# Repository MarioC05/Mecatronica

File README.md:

# Robot Sube-Escaleras

Proyecto de la asignatura **Mecatrónica** del **Grado en Ingeniería de Robótica Software** de la **Universidad Rey Juan Carlos (URJC)**.

## Componentes del grupo:

- Adrián Manzanares Romera: [Amanza17](https://github.com/Amanza17)
- Claudia Élez Mencía: [celezm](https://github.com/celezm)
- Mario Casero Sández: [MarioC05](https://github.com/MarioC05)
- Rebeca Castilla Puerta [rumbahuh](https://github.com/rumbahuh)

## Objetivo

Diseñar, fabricar y programar un robot terrestre capaz de **subir al menos un peldaño** de las escaleras del laboratorio III de la URJC, manteniendo la estabilidad y evitando obstáculos durante la aproximación.

### Requisitos principales

- Subir al menos un peldaño en **menos de 1 minuto**.
- Detectar y evitar obstáculos durante la aproximación, partiendo de **20 cm de la contrahuella**, dentro del tiempo establecido.
- No superar **25 × 25 × 25 cm** para el robot completo.
- Utilizar **baterías recargables**, sin alimentación por cable durante las pruebas.
- Diseñar y fabricar una **estructura propia**.
- Incorporar una interfaz para **iniciar y detener** el funcionamiento.
- Respetar la restricción de **locomoción sin ruedas** establecida en el enunciado.

## Diseño seleccionado

Durante la fase de diseño conceptual se estudiaron cuatro alternativas:

1. Robot cuadrúpedo tipo perro.
2. Robot bípedo con cuerpo horizontal y rueda loca delantera retráctil.
3. Robot serpiente modular.
4. Robot lineal tipo impresora 3D, con pie fijo y pie móvil.

La propuesta elegida para continuar el desarrollo es el **bípedo**. Consta de dos patas articuladas y un apoyo delantero mediante rueda loca que puede replegarse hacia atrás.

## Estructura del repositorio

```text
Mecatronica/
├── README.md
├── planificacion/
│   ├── diagrama_gantt
│   └── diagrama_pert
│   └── planificacion_nov
├── diseno_conceptual/
│   │   ├── matriz_calidad
│   │   └── matriz_seleccion
│   │   └── diseño_conceptual
├── diseno_detallado
│   ├── Eltronico.FCStd
│   ├── motores.pdf
│   └── piezas
│       ├── designed
│       │   ├── battery.FCStd
│       │   ├── ...
│       └── internet
│           ├── adafruit.FCStd
│           ├── ...
└── simulacion
    └── pybullet
        ├── eltronico.urdf
        ├── pybullet_meshes
        │   ├── Adafruit.stl
        │   ├── ...
        └── simulacion_estatica_escalon.py
└── eltronico_ws
    └── src  
        ├── eltronico
        ├── ir
        └── tui     
```

## Estado del proyecto

Actualmente, se está finalizando el montaje definitivo de las piezas del robot. El montaje de la electrónica está prácticamente finalizado, a expensas de la llegada de una PCB que integra los 2 reguladores de voltaje y algunas resistencias y la integración de un sensor infrarrojo para comandar al robot con un mando ir.

Respecto a la programación, se sigue trabajando en el controlador para la subida del escalón y en la migración e integración del código de MQTT y scripts de python a ROS2.

*Este es el robot a día 19 de noviembre*

En la carpeta [media](./media) se pueden encontrar distintas fotos y videos del montaje del robot y de pruebas de los motores.

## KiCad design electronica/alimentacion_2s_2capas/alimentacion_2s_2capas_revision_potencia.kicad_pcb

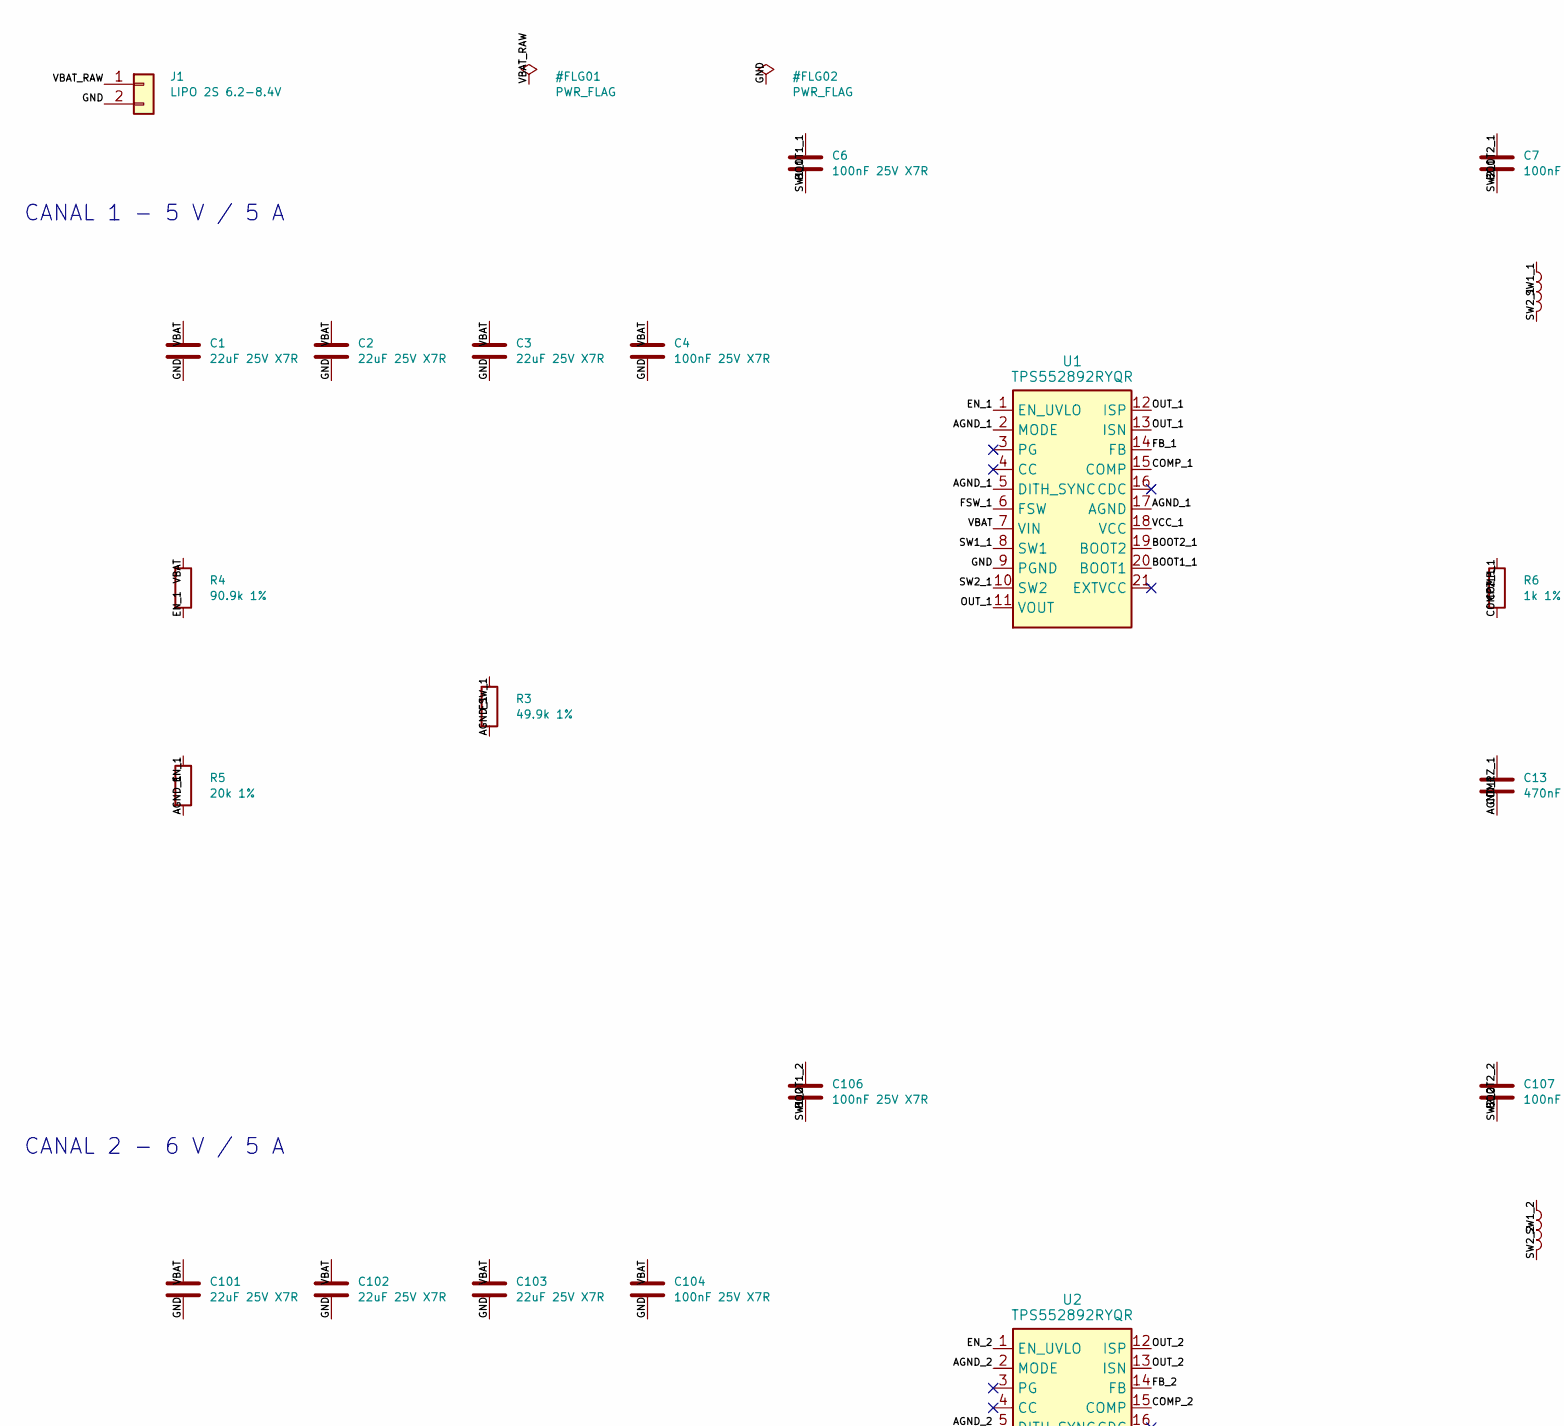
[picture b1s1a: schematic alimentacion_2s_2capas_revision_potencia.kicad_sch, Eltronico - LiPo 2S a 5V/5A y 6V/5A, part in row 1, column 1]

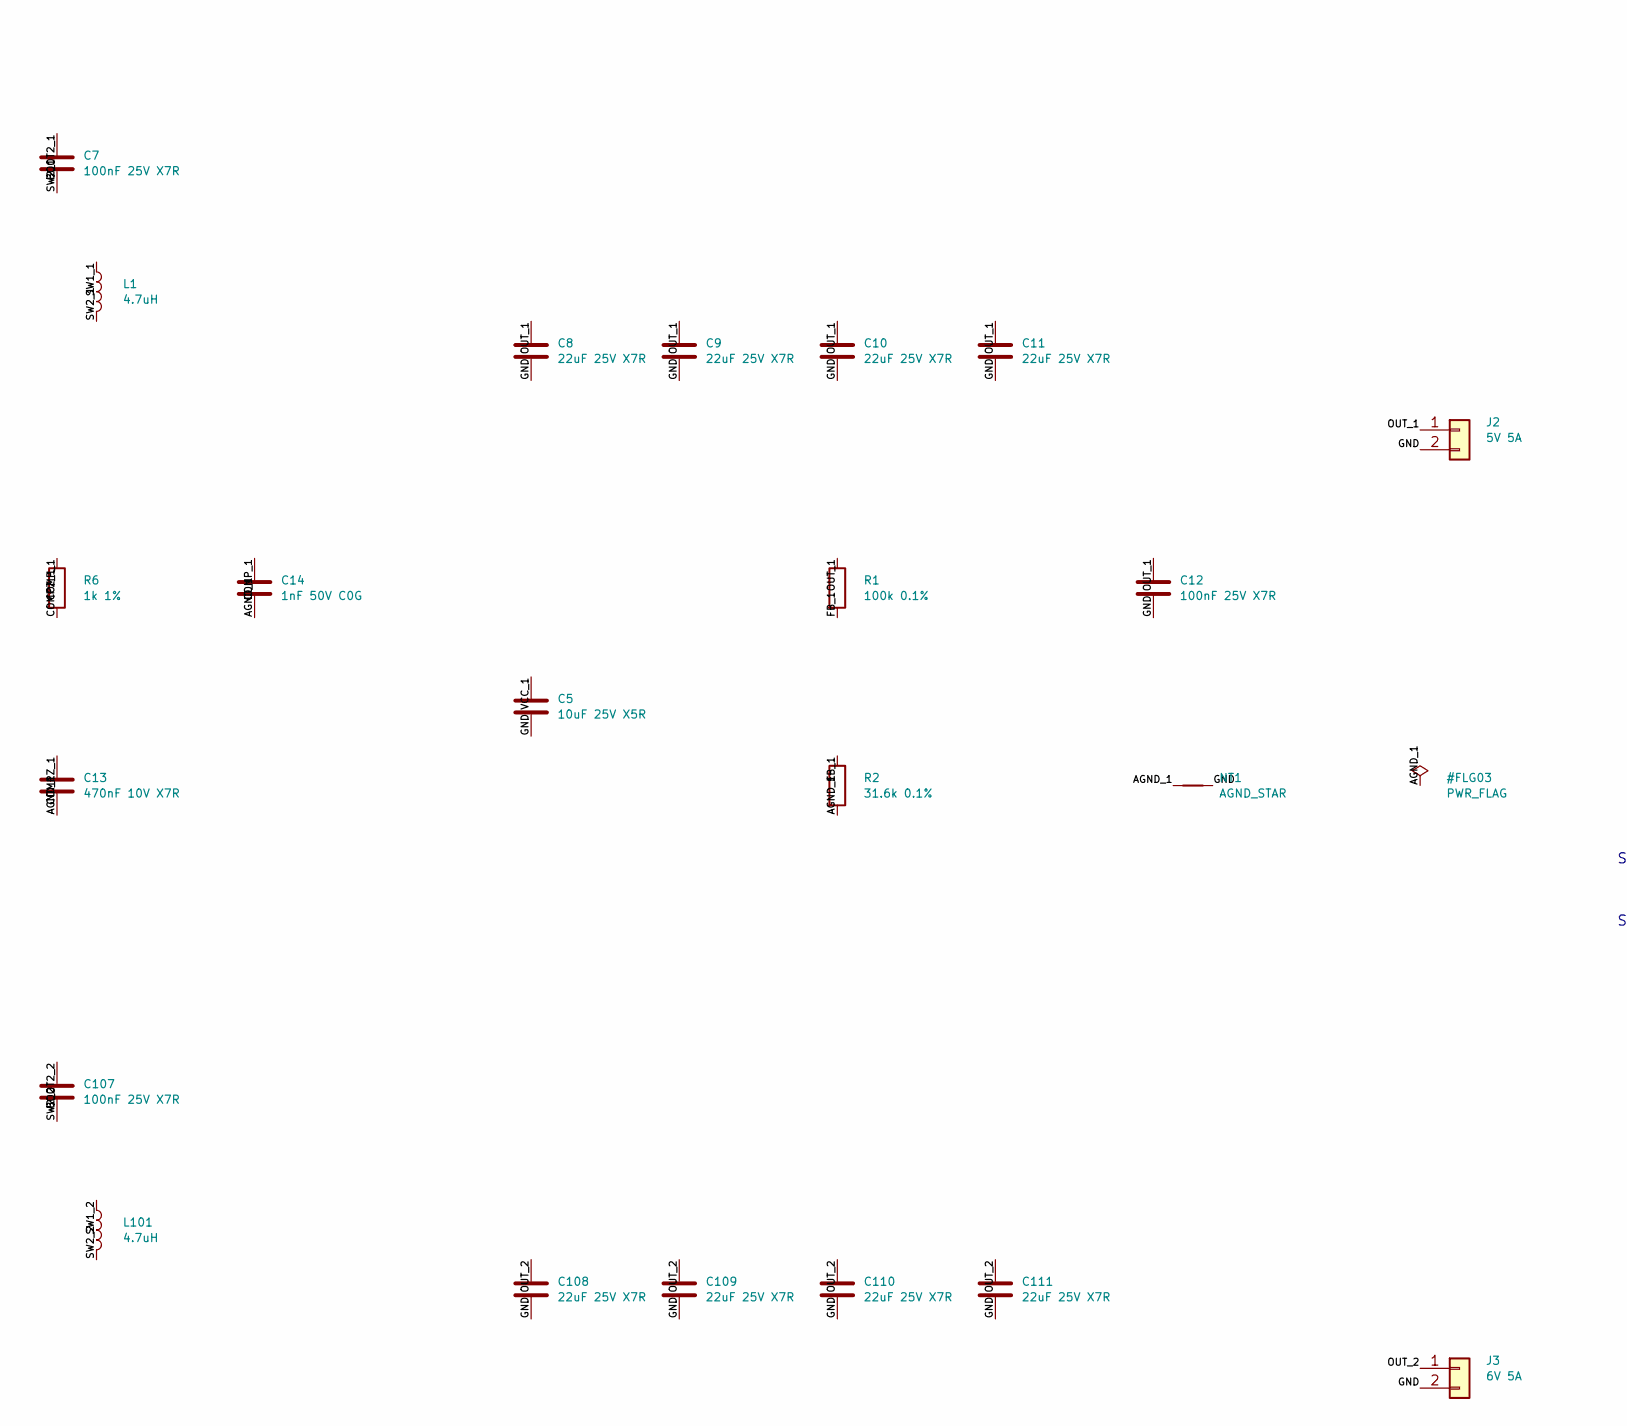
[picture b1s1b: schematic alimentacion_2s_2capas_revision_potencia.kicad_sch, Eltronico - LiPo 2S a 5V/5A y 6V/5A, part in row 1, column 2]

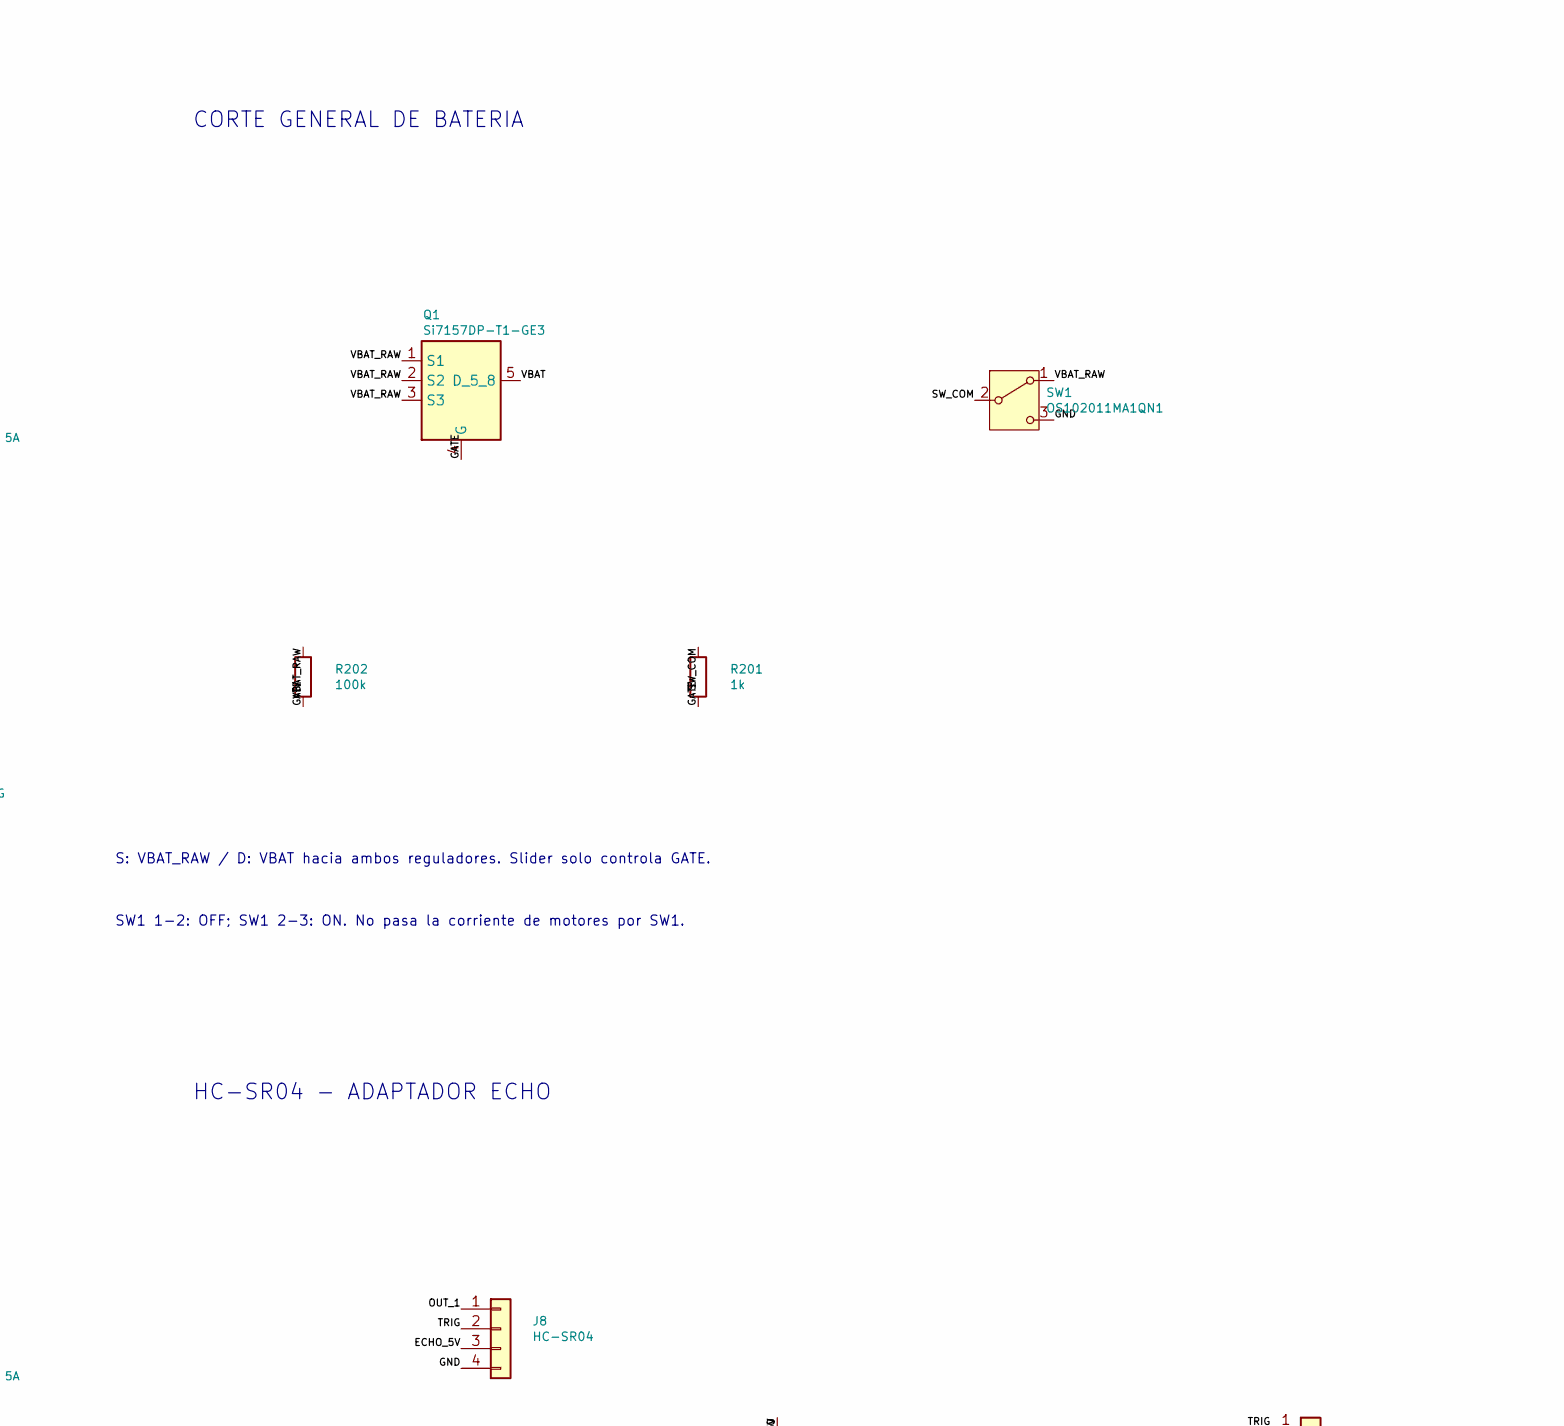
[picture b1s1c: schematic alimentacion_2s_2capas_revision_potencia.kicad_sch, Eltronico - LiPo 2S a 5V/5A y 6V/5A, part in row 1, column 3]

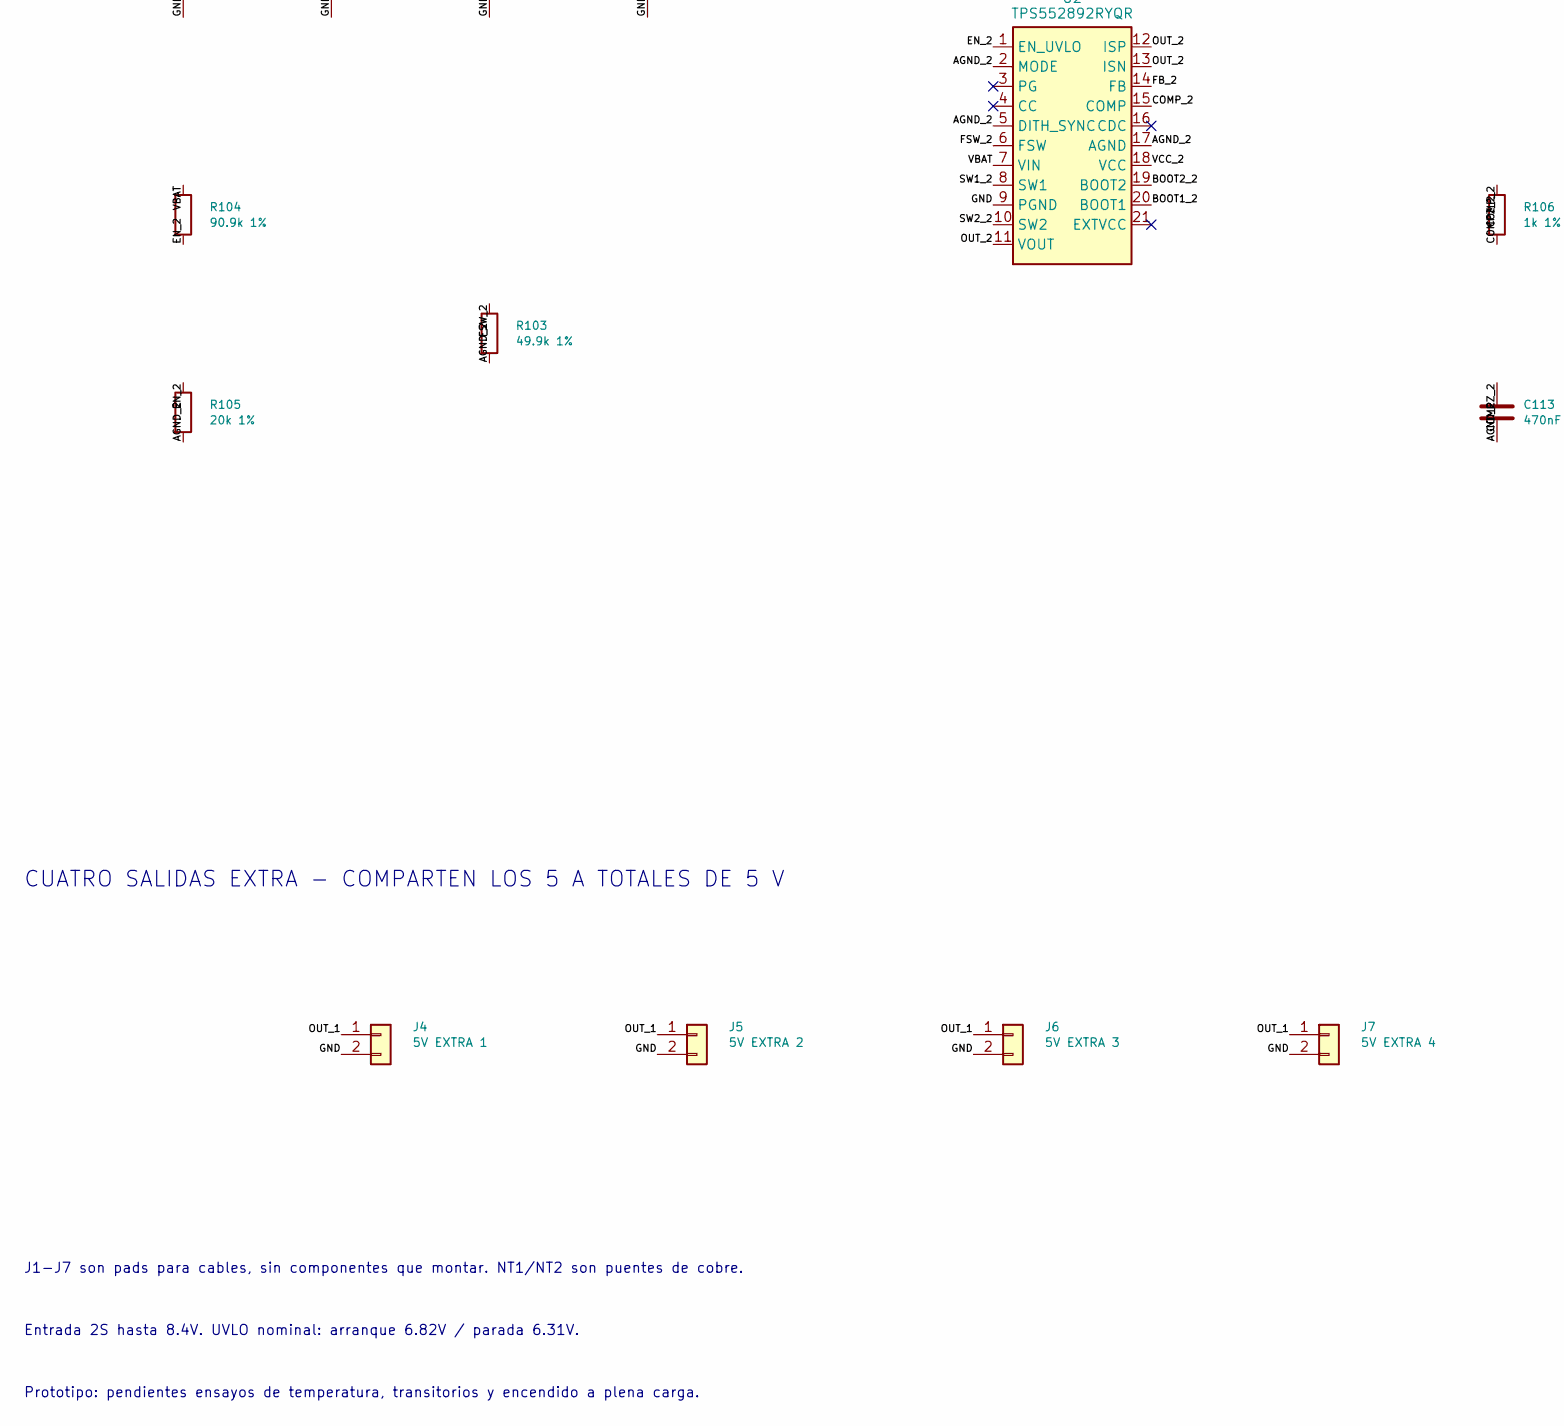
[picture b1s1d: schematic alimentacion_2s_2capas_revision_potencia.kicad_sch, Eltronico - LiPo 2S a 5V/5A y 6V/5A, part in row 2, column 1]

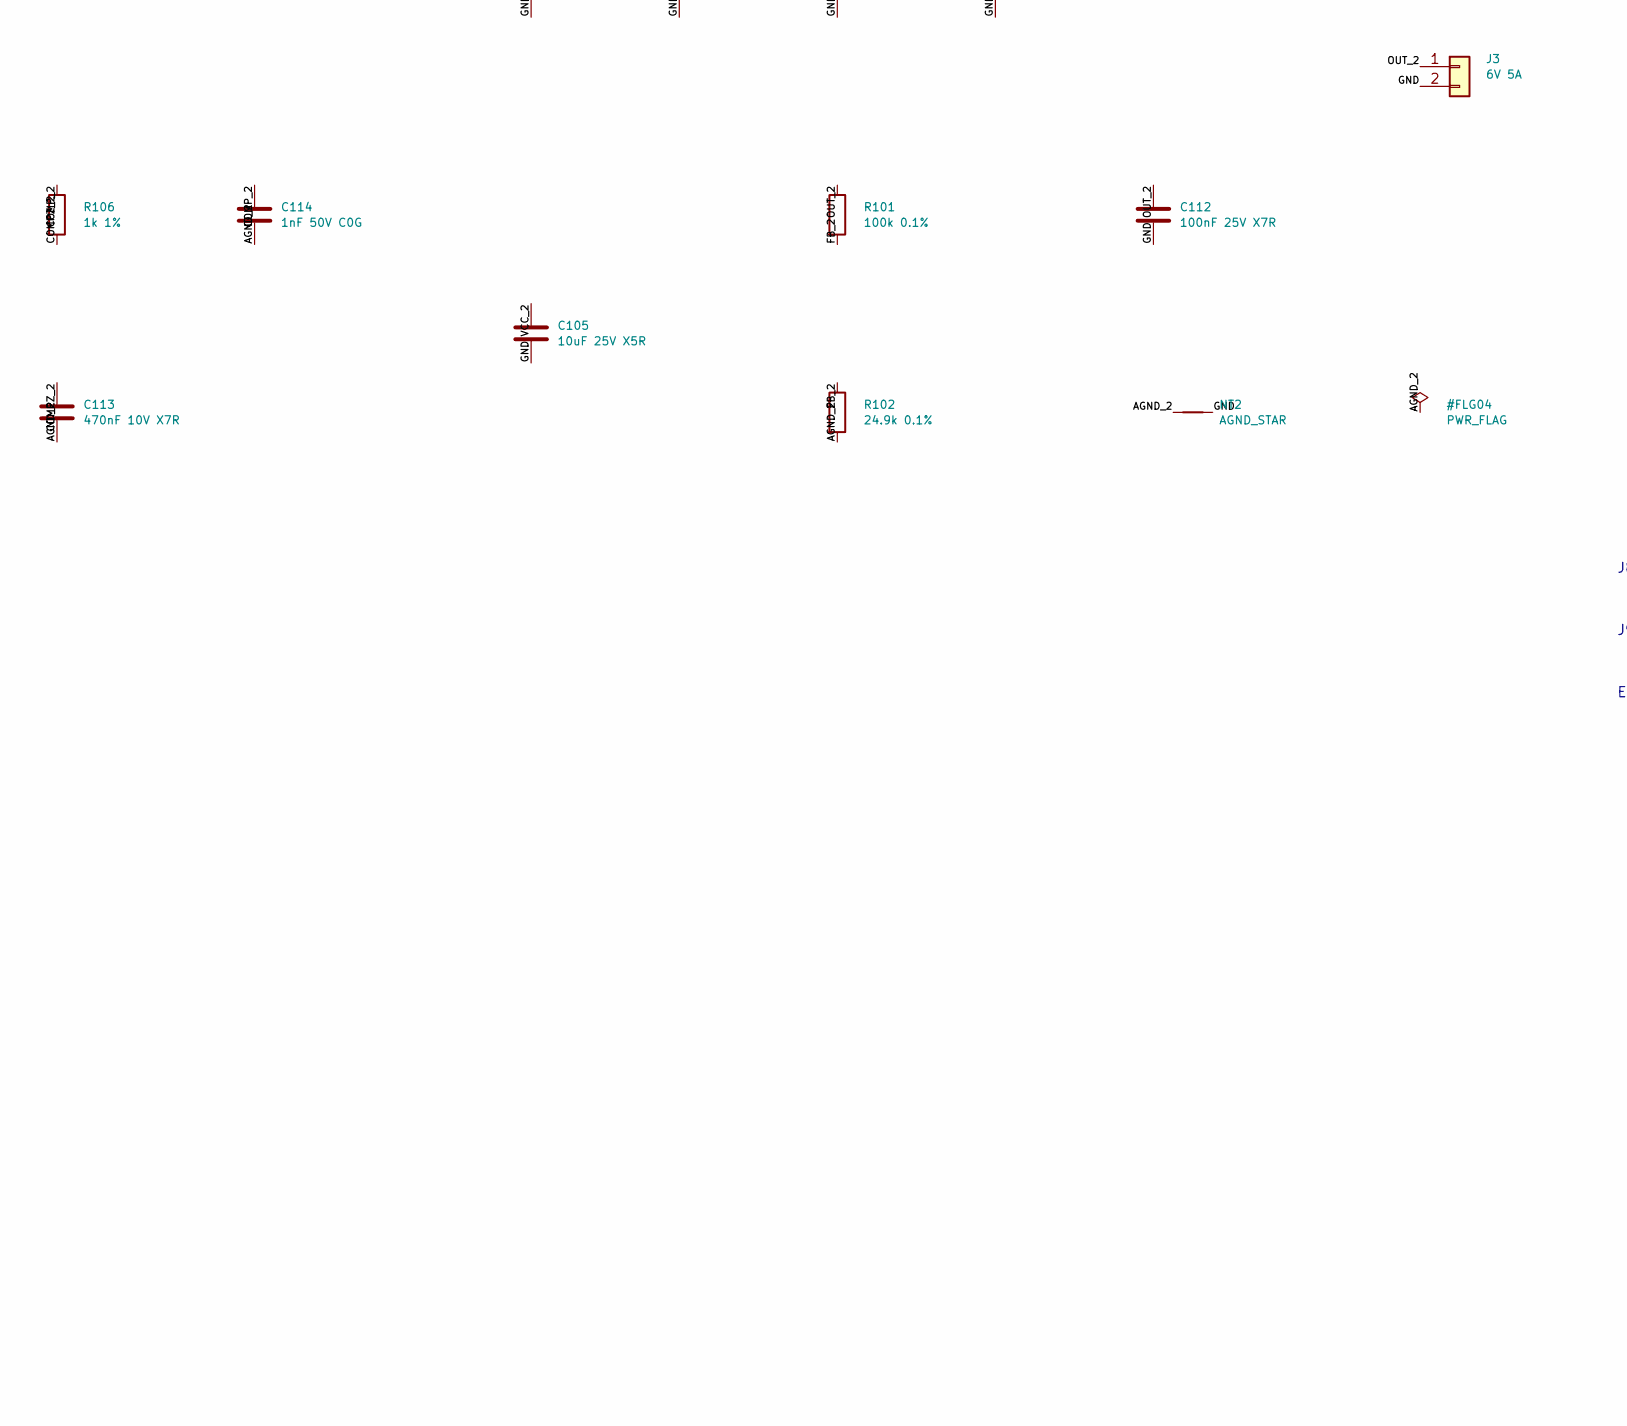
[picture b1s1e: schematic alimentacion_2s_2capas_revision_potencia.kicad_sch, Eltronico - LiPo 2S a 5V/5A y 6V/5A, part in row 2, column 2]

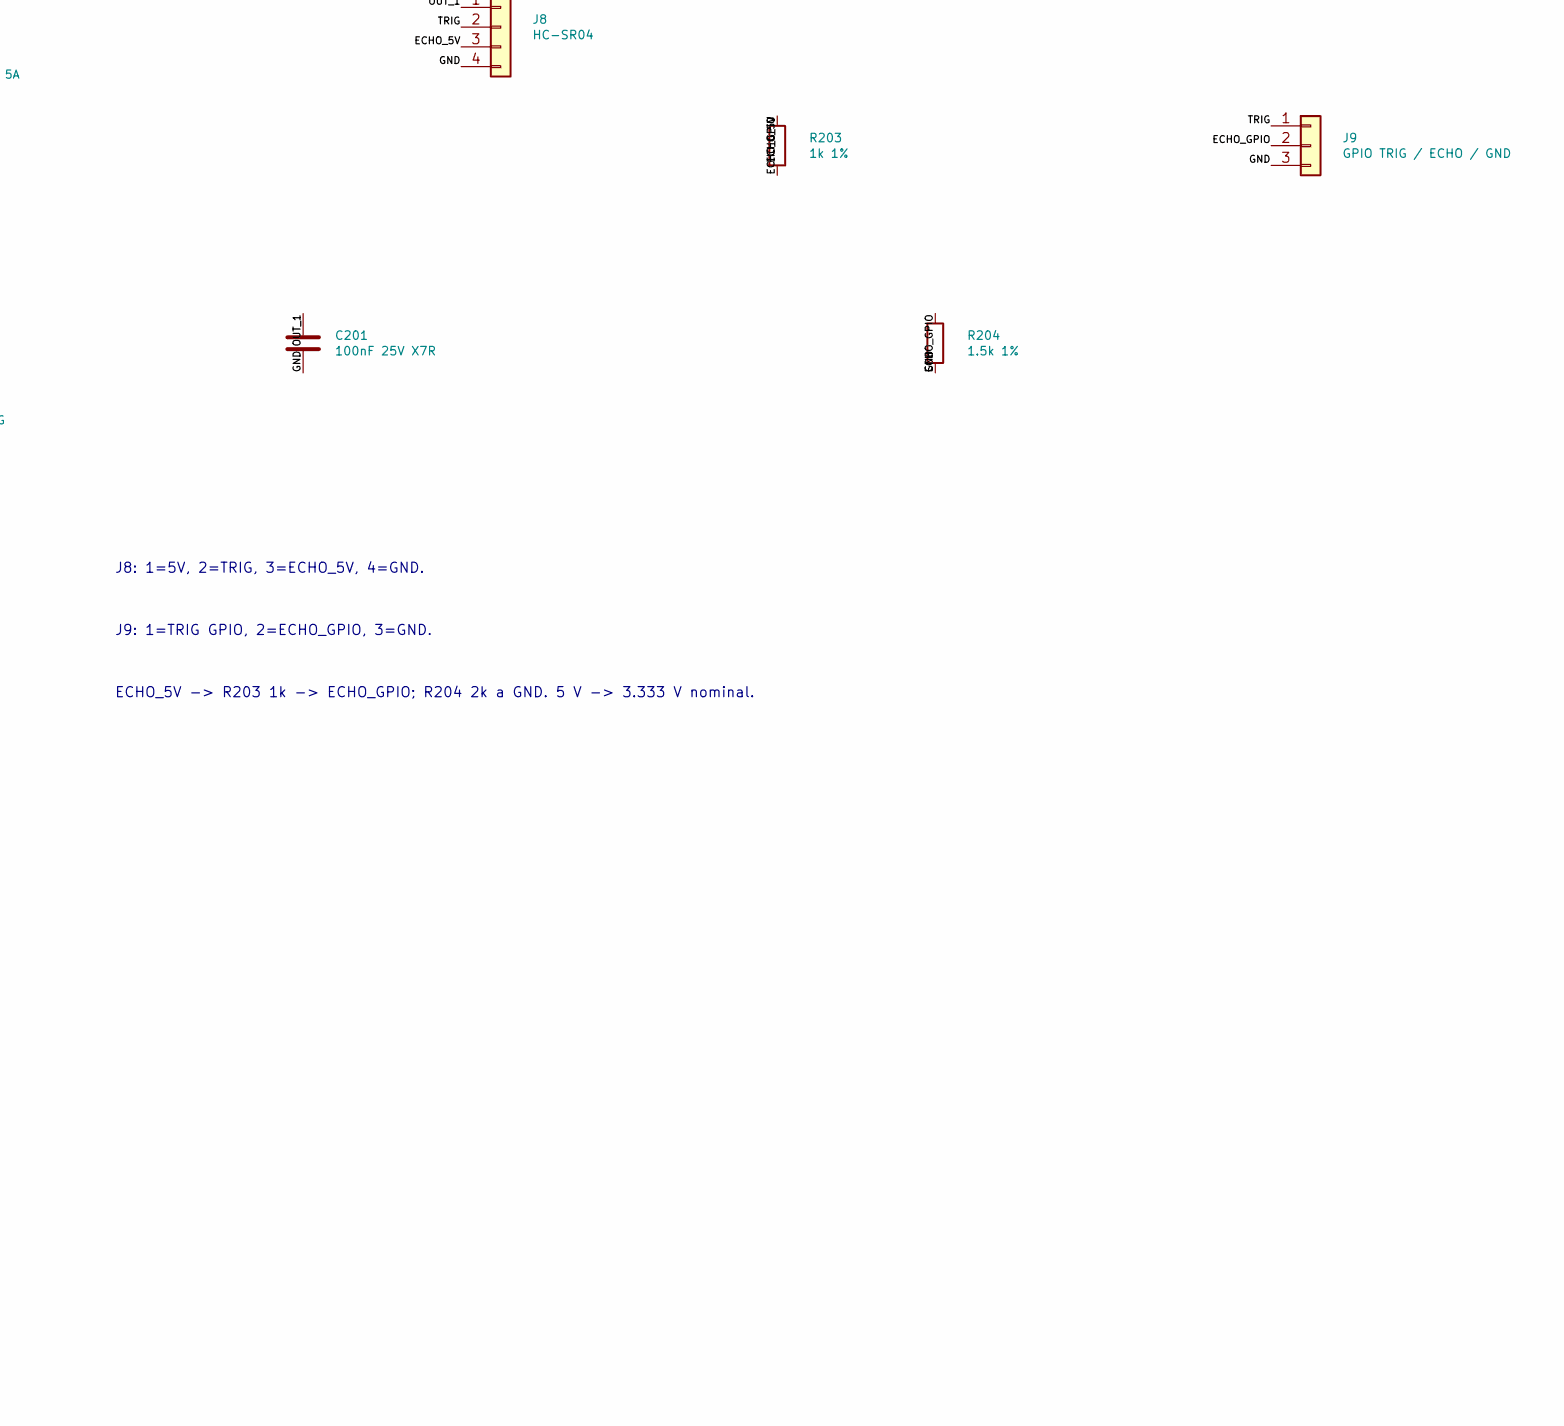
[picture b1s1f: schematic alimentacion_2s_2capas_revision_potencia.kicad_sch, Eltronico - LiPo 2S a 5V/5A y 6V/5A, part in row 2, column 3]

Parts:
C1, C2, C3, C8, C9, C10, C11, C101, C102, C103, C108, C109, C110, C111: 22uF 25V X7R; C_1210_3225Metric; Tolerance 10%; Voltage 25V; MPN GRM32ER71E226KE15L
C4, C6, C7, C12, C104, C106, C107, C112, C201: 100nF 25V X7R; C_0402_1005Metric; MPN GRM155R71E104KE14D
C5, C105: 10uF 25V X5R; C_0805_2012Metric; Tolerance 10%; Voltage 25V; MPN GRM21BR61E106KA73L
C13, C113: 470nF 10V X7R; C_0402_1005Metric; MPN GRM155R71A474KE15
C14, C114: 1nF 50V C0G; C_0402_1005Metric; MPN GRM1555C1H102JA01D
J1: LIPO 2S 6.2-8.4V; cable_2p_5mm
J2: 5V 5A; cable_2p_5mm
J3: 6V 5A; cable_2p_5mm
J4: 5V EXTRA 1; salida_2p_3p5mm
J5: 5V EXTRA 2; salida_2p_3p5mm
J6: 5V EXTRA 3; salida_2p_3p5mm
J7: 5V EXTRA 4; salida_2p_3p5mm
J8: HC-SR04; PinHeader_1x04_P2.54mm_Vertical; MPN 61300411121
J9: GPIO TRIG / ECHO / GND; PinHeader_1x03_P2.54mm_Vertical; MPN 61300311121
L1, L101: 4.7uH; L_Coilcraft_XAL7070-XXX; MPN XAL7070-472MEC
NT1, NT2: AGND_STAR; NetTie-2_SMD_Pad0.5mm
Q1: Si7157DP-T1-GE3; PowerPAK_SO-8_Single; MPN Si7157DP-T1-GE3
R1, R101: 100k 0.1%; R_0402_1005Metric; Tolerance 0.1%; MPN ERA2AEB1003X
R2: 31.6k 0.1%; R_0402_1005Metric; Tolerance 0.1%; MPN ERA2AEB3162X
R3, R103: 49.9k 1%; R_0402_1005Metric; Tolerance 1%; MPN RC0402FR-0749K9L
R4, R104: 90.9k 1%; R_0402_1005Metric; Tolerance 1%; MPN RC0402FR-0790K9L
R5, R105: 20k 1%; R_0402_1005Metric; Tolerance 1%; MPN RC0402FR-0720KL
R6, R106, R203: 1k 1%; R_0402_1005Metric; Tolerance 1%; MPN RC0402FR-071KL
R102: 24.9k 0.1%; R_0402_1005Metric; Tolerance 0.1%; MPN ERA2AEB2492X
R201: 1k; R_0402_1005Metric; Tolerance 1%; MPN RC0402FR-071KL
R202: 100k; R_0402_1005Metric; Tolerance 1%; MPN RC0402FR-07100KL
R204: 1.5k 1%; R_0402_1005Metric; Tolerance 1%; MPN RC0402FR-071K5L
SW1: OS102011MA1QN1; SW_Slide_SPDT_Angled_CK_OS102011MA1Q; MPN OS102011MA1QN1
U1, U2: TPS552892RYQR; TPS552892_RYQ0021A; MPN TPS552892RYQR

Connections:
/AGND_1: C13.2, C14.2, NT1.1, R2.2, R3.2, R5.2, U1.2 (MODE), U1.5 (DITH_SYNC), U1.17 (AGND)
/AGND_2: C113.2, C114.2, NT2.1, R102.2, R103.2, R105.2, U2.2 (MODE), U2.5 (DITH_SYNC), U2.17 (AGND)
/BOOT1_1: C6.1, U1.20 (BOOT1)
/BOOT1_2: C106.1, U2.20 (BOOT1)
/BOOT2_1: C7.1, U1.19 (BOOT2)
/BOOT2_2: C107.1, U2.19 (BOOT2)
/COMPZ_1: C13.1, R6.2
/COMPZ_2: C113.1, R106.2
/COMP_1: C14.1, R6.1, U1.15 (COMP)
/COMP_2: C114.1, R106.1, U2.15 (COMP)
/ECHO_5V: J8.3, R203.1
/ECHO_GPIO: J9.2, R203.2, R204.1
/EN_1: R4.2, R5.1, U1.1 (EN_UVLO)
/EN_2: R104.2, R105.1, U2.1 (EN_UVLO)
/FB_1: R1.2, R2.1, U1.14 (FB)
/FB_2: R101.2, R102.1, U2.14 (FB)
/FSW_1: R3.1, U1.6 (FSW)
/FSW_2: R103.1, U2.6 (FSW)
/GATE: Q1.4 (G), R201.2, R202.2
/GND: C1.2, C2.2, C3.2, C4.2, C5.2, C8.2, C9.2, C10.2, C11.2, C12.2, C101.2, C102.2, C103.2, C104.2, C105.2, C108.2, C109.2, C110.2, C111.2, C112.2, C201.2, J1.2, J2.2, J3.2, J4.2, J5.2, J6.2, J7.2, J8.4, J9.3, NT1.2, NT2.2, R204.2, SW1.3 (C), U1.9 (PGND), U2.9 (PGND)
/OUT_1: C8.1, C9.1, C10.1, C11.1, C12.1, C201.1, J2.1, J4.1, J5.1, J6.1, J7.1, J8.1, R1.1, U1.11 (VOUT), U1.12 (ISP), U1.13 (ISN)
/OUT_2: C108.1, C109.1, C110.1, C111.1, C112.1, J3.1, R101.1, U2.11 (VOUT), U2.12 (ISP), U2.13 (ISN)
/SW1_1: C6.2, L1.1, U1.8 (SW1)
/SW1_2: C106.2, L101.1, U2.8 (SW1)
/SW2_1: C7.2, L1.2, U1.10 (SW2)
/SW2_2: C107.2, L101.2, U2.10 (SW2)
/SW_COM: R201.1, SW1.2 (B)
/TRIG: J8.2, J9.1
/VBAT: C1.1, C2.1, C3.1, C4.1, C101.1, C102.1, C103.1, C104.1, Q1.5 (D_5_8), R4.1, R104.1, U1.7 (VIN), U2.7 (VIN)
/VBAT_RAW: J1.1, Q1.1 (S1), Q1.2 (S2), Q1.3 (S3), R202.1, SW1.1 (A)
/VCC_1: C5.1, U1.18 (VCC)
/VCC_2: C105.1, U2.18 (VCC)

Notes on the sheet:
J8: 1=5V, 2=TRIG, 3=ECHO_5V, 4=GND.
CORTE GENERAL DE BATERIA
J1-J7 son pads para cables, sin componentes que montar. NT1/NT2 son puentes de cobre.
Entrada 2S hasta 8.4V. UVLO nominal: arranque 6.82V / parada 6.31V.
CUATRO SALIDAS EXTRA - COMPARTEN LOS 5 A TOTALES DE 5 V
CANAL 1 - 5 V / 5 A
SW1 1-2: OFF; SW1 2-3: ON. No pasa la corriente de motores por SW1.
Prototipo: pendientes ensayos de temperatura, transitorios y encendido a plena carga.
S: VBAT_RAW / D: VBAT hacia ambos reguladores. Slider solo controla GATE.
HC-SR04 - ADAPTADOR ECHO
J9: 1=TRIG GPIO, 2=ECHO_GPIO, 3=GND.
ECHO_5V -> R203 1k -> ECHO_GPIO; R204 2k a GND. 5 V -> 3.333 V nominal.
CANAL 2 - 6 V / 5 A

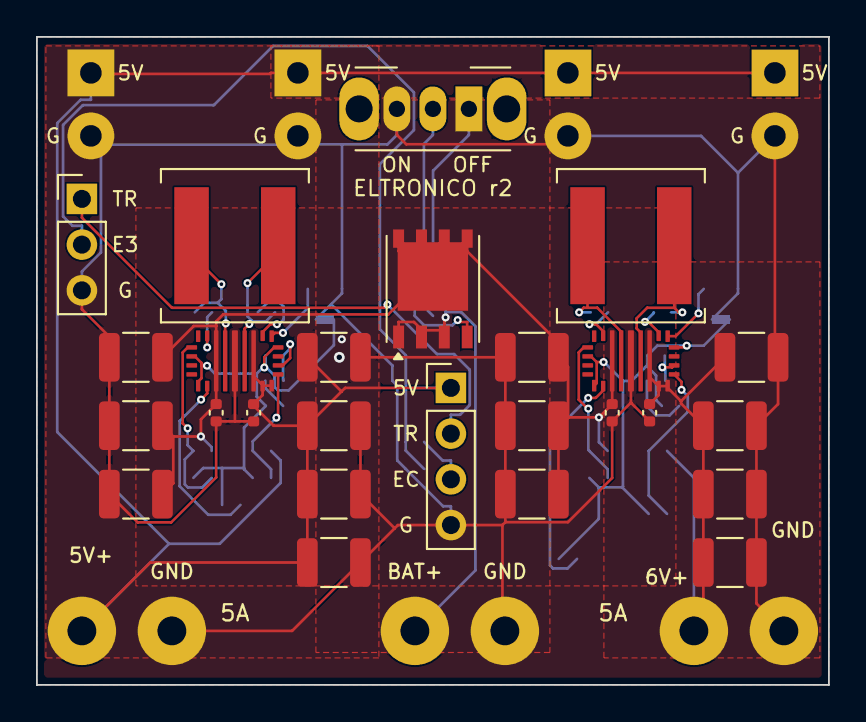
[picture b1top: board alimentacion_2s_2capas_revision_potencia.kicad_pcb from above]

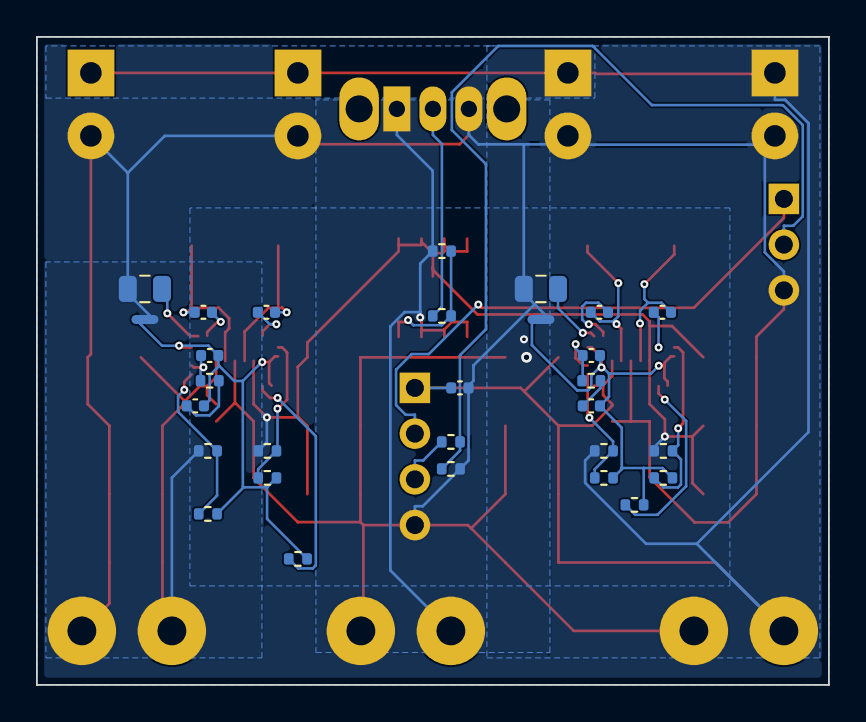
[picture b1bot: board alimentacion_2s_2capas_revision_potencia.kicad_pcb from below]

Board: 2 copper layers, 44.0 x 36.0 mm, 62 parts (29 on the bottom side), 32 nets.
